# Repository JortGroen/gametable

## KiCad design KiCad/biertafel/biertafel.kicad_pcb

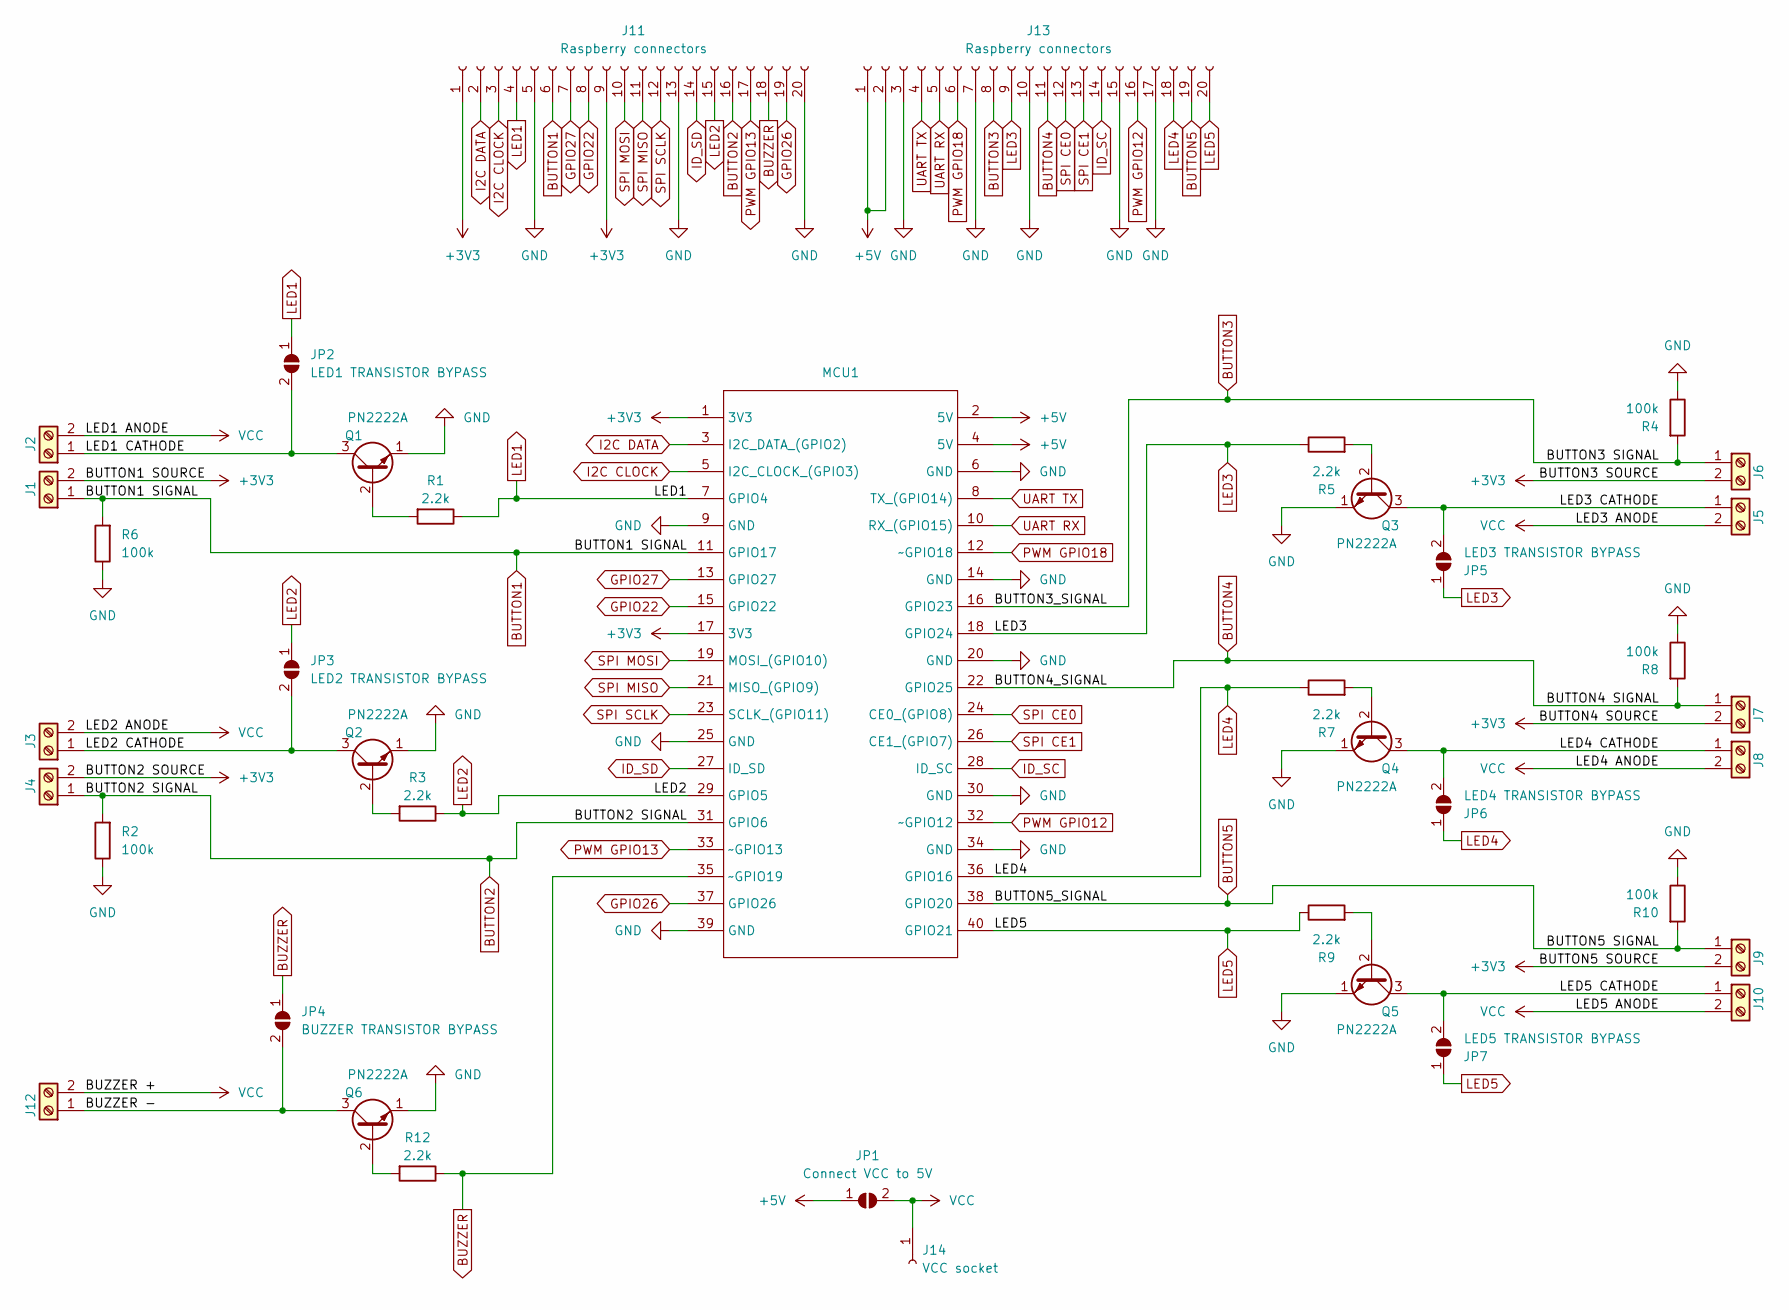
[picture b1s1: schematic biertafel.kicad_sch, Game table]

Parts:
J1, J2, J3, J4, J5, J6, J7, J8, J9, J10, J12: Screw_Terminal_01x02; 1725656
J11, J13: Raspberry connectors; PinSocket_1x20_P2.54mm_Vertical
J14: VCC socket; PinSocket_1x01_P2.54mm_Vertical
JP1: Connect VCC to 5V; SolderJumper-2_P1.3mm_Open_RoundedPad1.0x1.5mm
JP2: LED1 TRANSISTOR BYPASS; SolderJumper-2_P1.3mm_Open_RoundedPad1.0x1.5mm
JP3: LED2 TRANSISTOR BYPASS; SolderJumper-2_P1.3mm_Open_RoundedPad1.0x1.5mm
JP4: BUZZER TRANSISTOR BYPASS; SolderJumper-2_P1.3mm_Open_RoundedPad1.0x1.5mm
JP5: LED3 TRANSISTOR BYPASS; SolderJumper-2_P1.3mm_Open_RoundedPad1.0x1.5mm
JP6: LED4 TRANSISTOR BYPASS; SolderJumper-2_P1.3mm_Open_RoundedPad1.0x1.5mm
JP7: LED5 TRANSISTOR BYPASS; SolderJumper-2_P1.3mm_Open_RoundedPad1.0x1.5mm
MCU1: Raspberry PI Zero W
Q1, Q2, Q3, Q4, Q5, Q6: PN2222A; TO-92_Inline
R1, R3, R5, R7, R9, R12: 2.2k; R_Axial_DIN0207_L6.3mm_D2.5mm_P10.16mm_Horizontal
R2, R4, R6, R8, R10: 100k; R_Axial_DIN0207_L6.3mm_D2.5mm_P10.16mm_Horizontal

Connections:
+3V3: J1.2, J4.2, J6.2, J7.2, J9.2, J11.1, J11.9, MCU1.1 (3V3), MCU1.17 (3V3)
+5V: J13.1, J13.2, JP1.1 (A), MCU1.2 (5V), MCU1.4 (5V)
/BUZZER -: J12.1, JP4.2 (B), Q6.3 (C)
/LED1 CATHODE: J2.1, JP2.2 (B), Q1.3 (C)
/LED2 CATHODE: J3.1, JP3.2 (B), Q2.3 (C)
/LED3 CATHODE: J5.1, JP5.2 (B), Q3.3 (C)
/LED4 CATHODE: J8.1, JP6.2 (B), Q4.3 (C)
/LED5 CATHODE: J10.1, JP7.2 (B), Q5.3 (C)
BUTTON1: J1.1, J11.6, MCU1.11 (GPIO17), R6.2
BUTTON2: J4.1, J11.16, MCU1.31 (GPIO6), R2.2
BUTTON3: J6.1, J13.8, MCU1.16 (GPIO23), R4.2
BUTTON4: J7.1, J13.11, MCU1.22 (GPIO25), R8.2
BUTTON5: J9.1, J13.19, MCU1.38 (GPIO20), R10.2
BUZZER: J11.18, JP4.1 (A), MCU1.35 (~GPIO19), R12.1
GND: J11.5, J11.13, J11.20, J13.3, J13.7, J13.10, J13.15, J13.17, MCU1.6 (GND), MCU1.9 (GND), MCU1.14 (GND), MCU1.20 (GND), MCU1.25 (GND), MCU1.30 (GND), MCU1.34 (GND), MCU1.39 (GND), Q1.1 (E), Q2.1 (E), Q3.1 (E), Q4.1 (E), Q5.1 (E), Q6.1 (E), R2.1, R4.1, R6.1, R8.1, R10.1
GPIO22: J11.8, MCU1.15 (GPIO22)
GPIO26: J11.19, MCU1.37 (GPIO26)
GPIO27: J11.7, MCU1.13 (GPIO27)
I2C CLOCK: J11.3, MCU1.5 (I2C_CLOCK_(GPIO3))
I2C DATA: J11.2, MCU1.3 (I2C_DATA_(GPIO2))
ID_SC: J13.14, MCU1.28 (ID_SC)
ID_SD: J11.14, MCU1.27 (ID_SD)
LED1: J11.4, JP2.1 (A), MCU1.7 (GPIO4), R1.1
LED2: J11.15, JP3.1 (A), MCU1.29 (GPIO5), R3.1
LED3: J13.9, JP5.1 (A), MCU1.18 (GPIO24), R5.1
LED4: J13.18, JP6.1 (A), MCU1.36 (GPIO16), R7.1
LED5: J13.20, JP7.1 (A), MCU1.40 (GPIO21), R9.1
unnamed: Q1.2 (B), R1.2
unnamed: Q2.2 (B), R3.2
unnamed: Q3.2 (B), R5.2
unnamed: Q4.2 (B), R7.2
unnamed: Q5.2 (B), R9.2
unnamed: Q6.2 (B), R12.2
PWM GPIO12: J13.16, MCU1.32 (~GPIO12)
PWM GPIO13: J11.17, MCU1.33 (~GPIO13)
PWM GPIO18: J13.6, MCU1.12 (~GPIO18)
SPI CE0: J13.12, MCU1.24 (CE0_(GPIO8))
SPI CE1: J13.13, MCU1.26 (CE1_(GPIO7))
SPI MISO: J11.11, MCU1.21 (MISO_(GPIO9))
SPI MOSI: J11.10, MCU1.19 (MOSI_(GPIO10))
SPI SCLK: J11.12, MCU1.23 (SCLK_(GPIO11))
UART RX: J13.5, MCU1.10 (RX_(GPIO15))
UART TX: J13.4, MCU1.8 (TX_(GPIO14))
VCC: J2.2, J3.2, J5.2, J8.2, J10.2, J12.2, J14.1, JP1.2 (B)

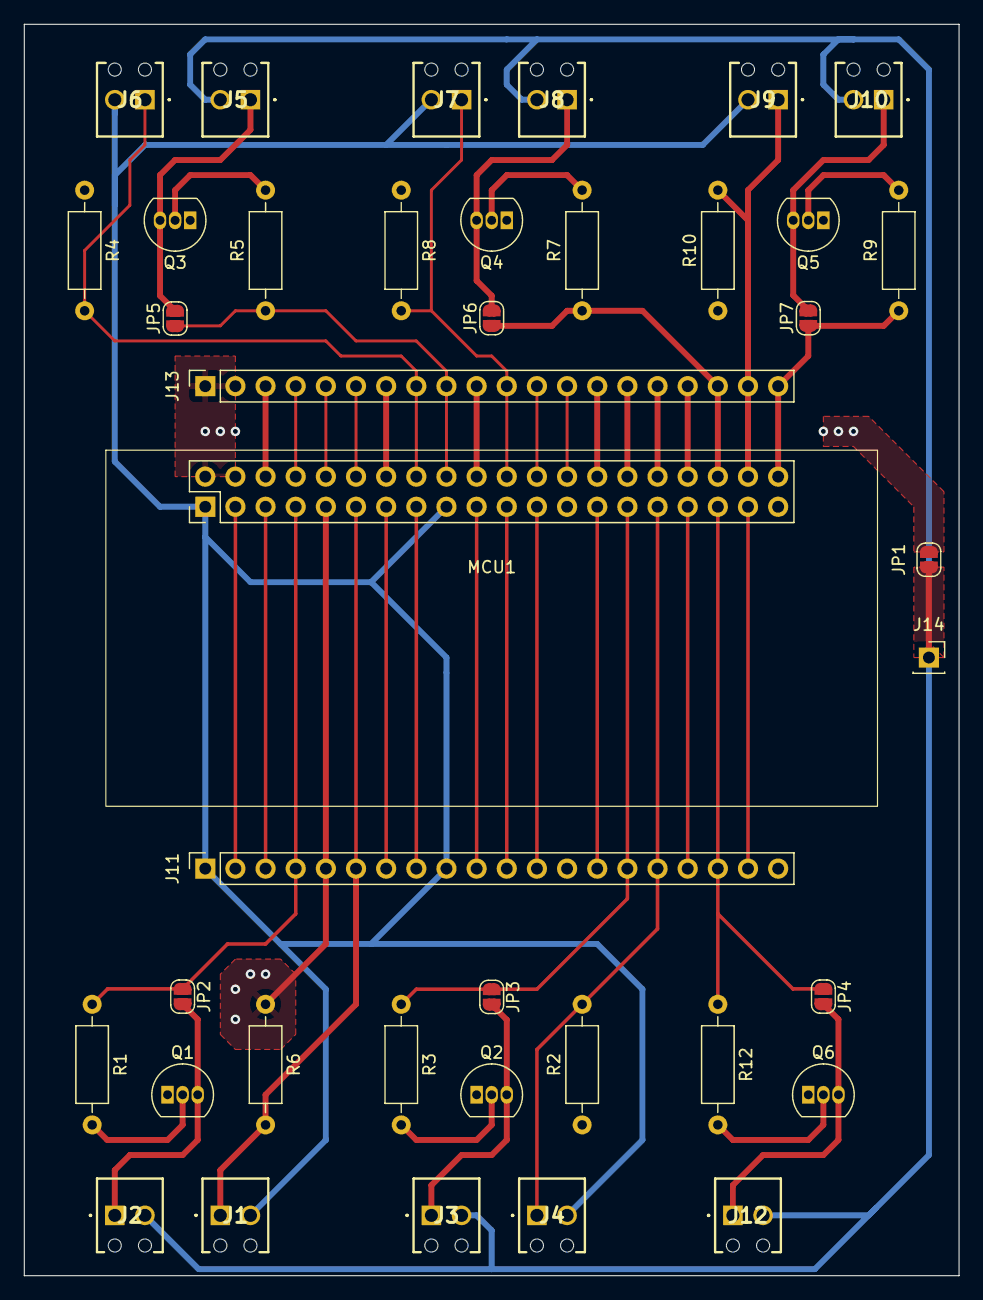
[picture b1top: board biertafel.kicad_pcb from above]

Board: 2 copper layers, 78.7 x 105.4 mm, 39 parts (0 on the bottom side), 44 nets.

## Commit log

2022-12-01 Initial build for NodeMCU v1 with roulette demo
2022-12-05 added main menu new helper functions: blinkedLed, waitforpress
2022-12-05 added main menu functionallity
2022-12-05 different style for roulette game added
2022-12-05 new pick a tooth game
2022-12-07 bug fix: re-pressing teeth
2022-12-07 new game: crashpilot
2022-12-07 added party mode
2023-02-25 Added Buzzer functionality
2023-02-25 improved speed of roulette1 game added buzzer to roulette1 game
2023-02-25 created the single tune Music generator program for checking delay times of button presses
2023-02-25 Now the music generator gives you the music code instantly
2023-02-25 added celebration and put it to the end of roulette1
2023-06-14 Moved arduino files to designated folder as preparation to the switch to Raspberry PI Zero W
2023-06-14 Added initial KiCad PCB design for Raspberry PI Zero W version
2023-06-14 Raspberry PI Zero W symbol now contains all functionalities per port
2023-07-10 First version of schematic finished, started with PCB layout
2023-07-10 In PCB layout, placed the objects to aprox position
2023-09-22 moved files inside "gametable" dir, according to Arduino requirements. Tried to fix bug in crashpilot where green gets blamed for nothing introduced beeps in other games that didn't have any
2023-09-22 New Game! Wack a mole, has same player menu as crash pilot. Press the button in time!
2024-02-14 PCB layout V0.1
2024-02-15 added compatibility for Mini version
